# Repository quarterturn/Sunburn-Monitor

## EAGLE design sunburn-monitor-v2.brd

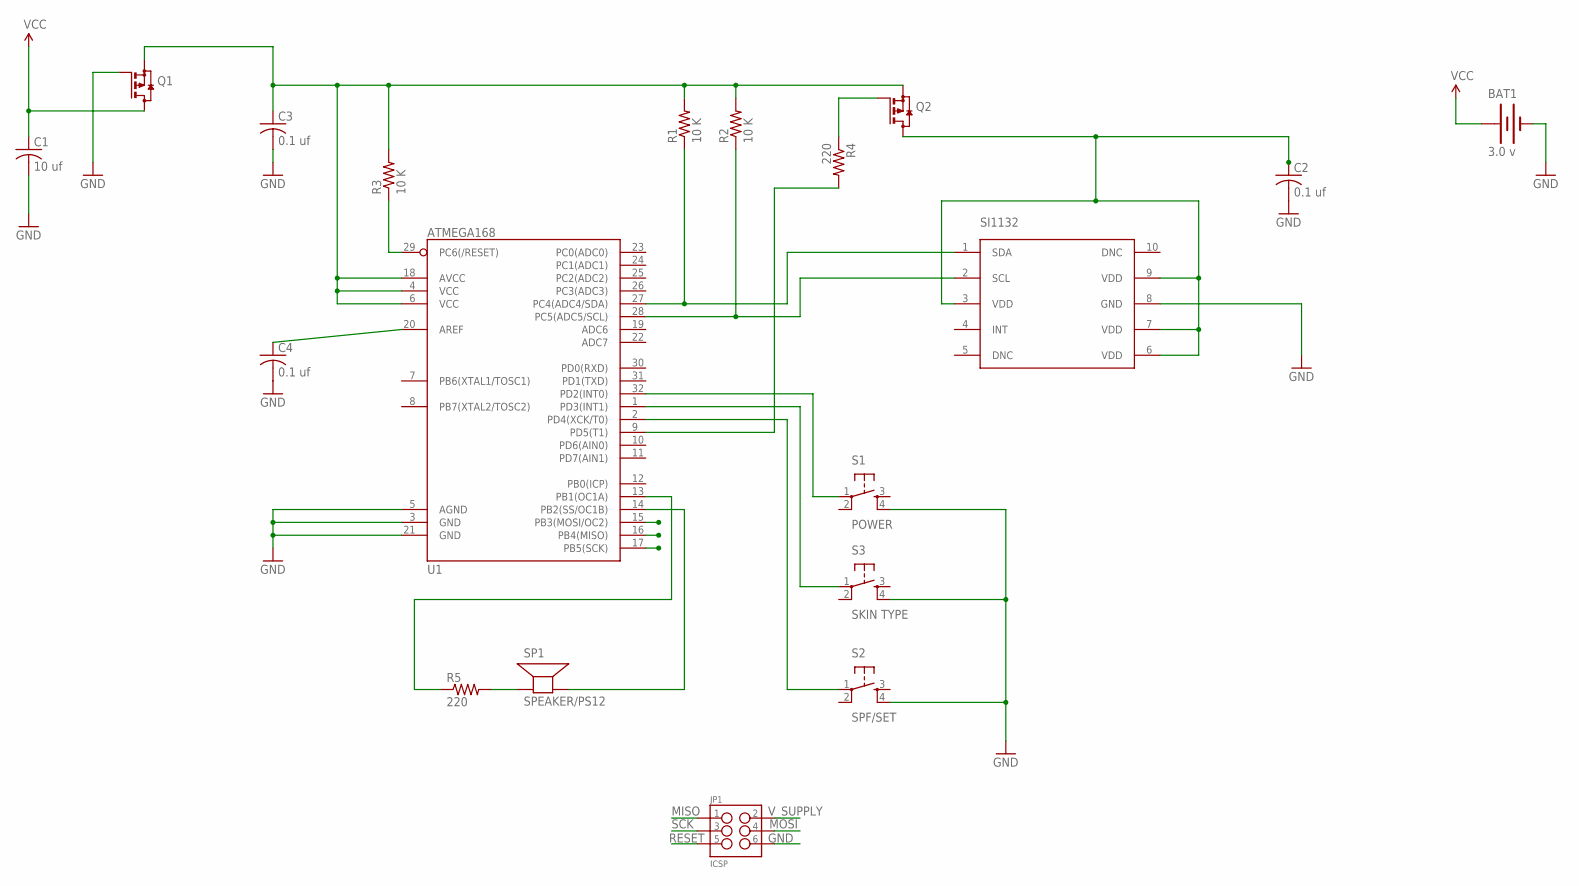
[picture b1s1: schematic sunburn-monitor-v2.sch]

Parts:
BAT1: 3.0 v; BATTCON_20MM
C1: 10 uf; C2012
C2, C3, C4: 0.1 uf; C2012
JP1: ICSP; 2X3-NS
Q1, Q2: SI2333DDS; SOT23
R1, R2, R3: 10 K; R2012
R4, R5: 220; R2012
S1: POWER; TACTILE_SWITCH_SMD
S2: SPF/SET; TACTILE_SWITCH_SMD
S3: SKIN TYPE; TACTILE_SWITCH_SMD
SP1: SPEAKER/PS12; PS12
U1: ATMEGA168; TQFP32-08
U2: SI1132; QFN-10

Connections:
GND: BAT1.2 (-), C1.2, C2.2, C3.2, C4.2, JP1.6, Q1.1 (G), S1.4, S2.4, S3.4, U1.3 (GND), U1.5 (AGND), U1.21 (GND), U2.8 (GND)
MISO: JP1.1, U1.16 (PB4(MISO))
MOSI: JP1.4, U1.15 (PB3(MOSI/OC2))
unnamed: R1.1, U1.27 (PC4(ADC4/SDA)), U2.1 (SDA)
unnamed: C4.1, U1.20 (AREF)
unnamed: R2.1, U1.28 (PC5(ADC5/SCL)), U2.2 (SCL)
unnamed: C2.1, Q2.3 (D), U2.3 (VDD), U2.6 (VDD), U2.7 (VDD), U2.9 (VDD)
unnamed: Q2.1 (G), R4.1
unnamed: S1.1, U1.32 (PD2(INT0))
unnamed: S3.1, U1.1 (PD3(INT1))
unnamed: S2.1, U1.2 (PD4(XCK/T0))
unnamed: R4.2, U1.9 (PD5(T1))
unnamed: R5.1, U1.13 (PB1(OC1A))
unnamed: R5.2, SP1.P$1 (+)
unnamed: SP1.P$2 (-), U1.14 (PB2(SS/OC1B))
RESET: JP1.5, R3.1, U1.29 (PC6(/RESET))
SCK: JP1.3, U1.17 (PB5(SCK))
VCC: BAT1.1 (+), C1.1, Q1.3 (D)
V_SUPPLY: C3.1, JP1.2, Q1.2 (S), Q2.2 (S), R1.2, R2.2, R3.2, U1.4 (VCC), U1.6 (VCC), U1.18 (AVCC)

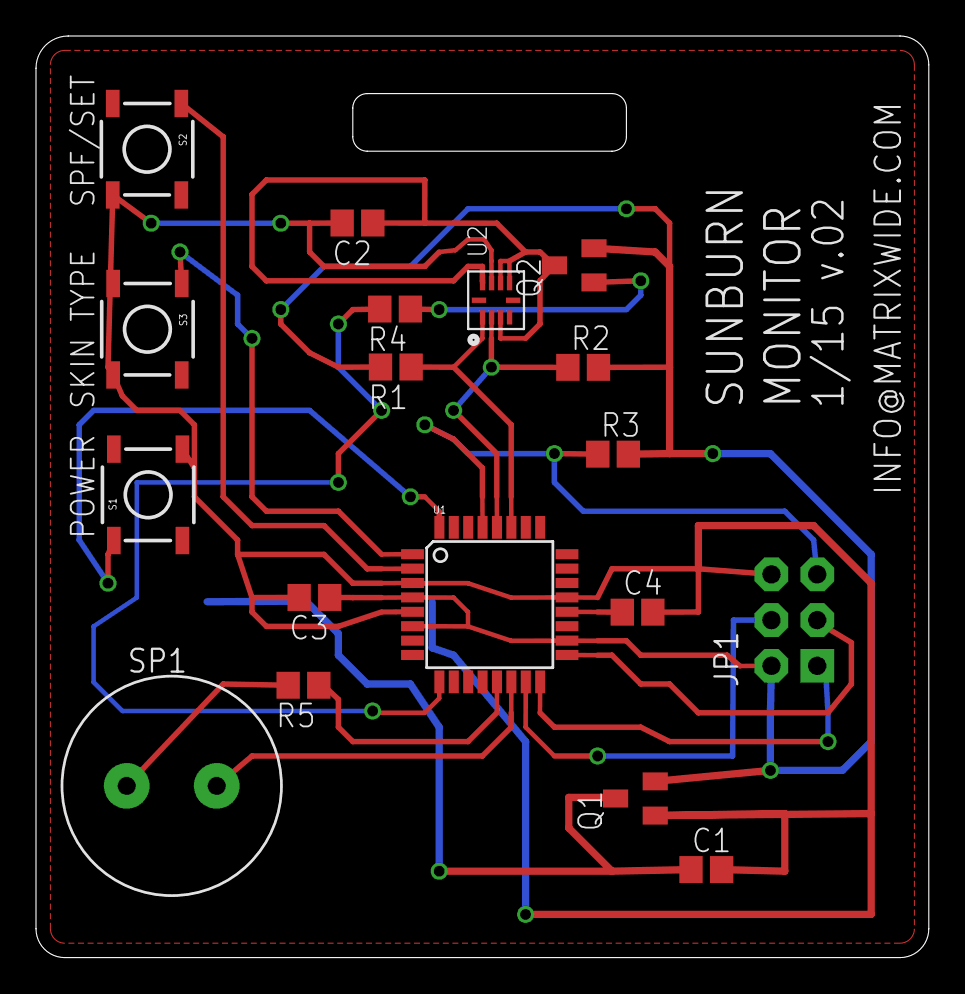
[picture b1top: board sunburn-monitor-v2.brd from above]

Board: 2 copper layers, 49.6 x 51.2 mm, 19 parts (1 on the bottom side), 19 nets.

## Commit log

2015-03-04 Sunburn Monitor V 0.2 - Tested OK
2015-03-04 Added Eagle files for v 0.2 board
2015-04-05 updated requirement for 8 mHz MCU speed; added docs on fuses

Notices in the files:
parts and their libraries:
SparkFun-DigitalIC: Licensing: Creative Commons ShareAlike 4.0 International - https://creativecommons.org/licenses/by-sa/4.0
